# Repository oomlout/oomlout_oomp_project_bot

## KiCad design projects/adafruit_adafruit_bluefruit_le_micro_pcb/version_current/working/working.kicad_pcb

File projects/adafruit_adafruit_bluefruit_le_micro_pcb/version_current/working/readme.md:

# OOMP Project  
## Adafruit-Bluefruit-LE-Micro-PCB  by adafruit  
  
oomp key: oomp_projects_flat_adafruit_adafruit_bluefruit_le_micro_pcb  
(snippet of original readme)  
  
-- Adafruit Bluefruit LE Micro PCB (Discontinued)  
<a href="http://www.adafruit.com/products/2661"><br/>  
See the part listing in the Adafruit shop</a>  
  
DISCONTINUED  
Check out the [Adafruit Feather 32u4 Bluefruit LE](https://www.adafruit.com/products/2829), it's an awesome upgrade!  
  
PCB files for Adafruit Bluefruit LE Micro. Format is EagleCAD.  
- https://www.adafruit.com/product/2661  
  
--- License  
  
Adafruit invests time and resources providing this open source design, please support Adafruit and open-source hardware by purchasing products from [Adafruit](https://www.adafruit.com)!  
  
All text above must be included in any redistribution  
  
Designed by Limor Fried/Ladyada for Adafruit Industries.  
Creative Commons Attribution/Share-Alike, all text above must be included in any redistribution.   
See license.txt for additional information.  
  
  full source readme at [readme_src.md](readme_src.md)  
  
source repo at: [https://github.com/adafruit/Adafruit-Bluefruit-LE-Micro-PCB](https://github.com/adafruit/Adafruit-Bluefruit-LE-Micro-PCB)  
## Board  

## Schematic  

[schematic pdf](working_schematic.pdf)  
## Images

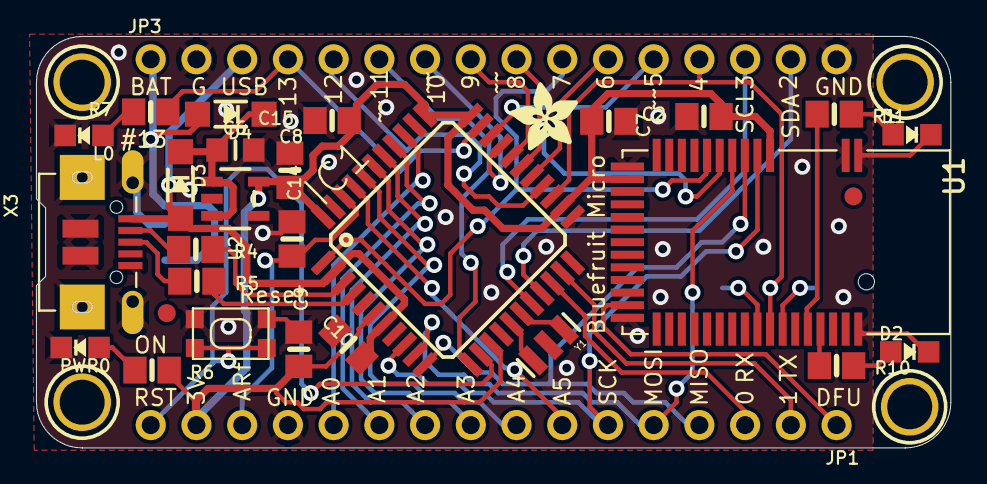
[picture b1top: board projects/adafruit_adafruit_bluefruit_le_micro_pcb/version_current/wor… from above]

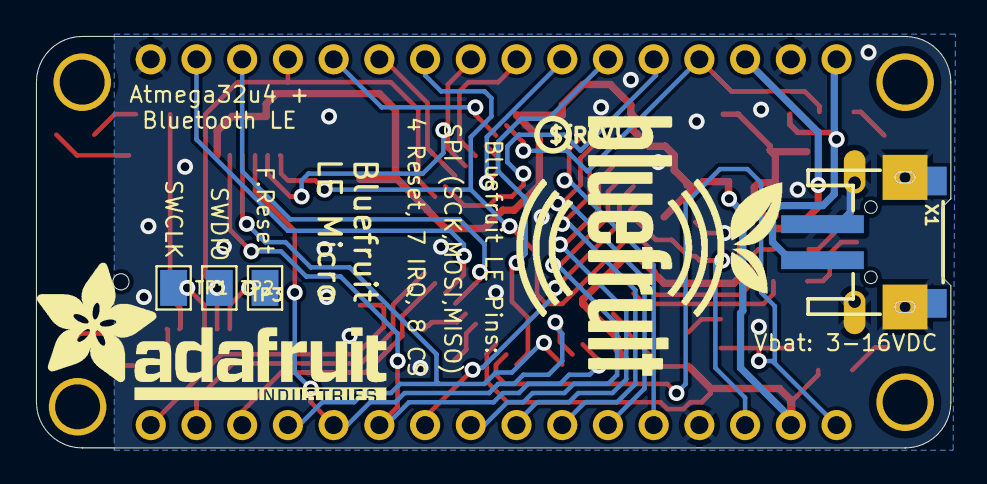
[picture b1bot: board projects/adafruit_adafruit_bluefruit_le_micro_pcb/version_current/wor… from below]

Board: 2 copper layers, 50.8 x 22.9 mm, 42 parts (7 on the bottom side), 45 nets.

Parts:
C2, C9: 1uF; 0805-NO
C6: 10µF; _0805MP
C7, C8: 10µF; 0805-NO
C10: 0.1uF; 0805_10MGAP
C14, C15: 0.1uF; 0805-NO
D1: RED; CHIPLED_0805_NOOUTLINE
D2: BLUE; CHIPLED_0805_NOOUTLINE
D3, D4: MBR120; SOD-123
IC1: ATMEGA32U4-AU; TQFP44
JP1, JP3: 1X16_ROUND
L0: RED; CHIPLED_0805_NOOUTLINE
PWR0: GREEN; CHIPLED_0805_NOOUTLINE
R1, R6, R7, R10: 2.2K; 0805-NO
R4, R5: 22; 0805-NO
SW1: SPST_TACT-KMR2; KMR2
TP1: SWCLK; PAD-1.5X2.0
TP2, TP3: SWDIO; PAD-1.5X2.0
U1: MBT40; BLE_MODULE_RAYTAC_MDBT40
U2: MIC5225-3.3; SOT23-5
U$6, U$24, U$31, U$32: MOUNTINGHOLE2.5; MOUNTINGHOLE_2.5_PLATED
U$7: ADAFRUIT_3.5MM
U$9: ADAFRUIT_TEXT_20MM
U$15: BLUEFRUITLOGO_150MM
U$23: PCBFEAT-REV-040
U$34, U$35: FIDUCIAL""; FIDUCIAL_1MM
X1: JSTPH; JSTPH2
X3: microUSB; 4UCONN_20329
Y1: 8MHz; RESONATOR-SMD

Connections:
0: IC1.20, JP1.3
1: IC1.21, JP1.2
2: IC1.19, JP3.15
3: IC1.18, JP3.14
4_SWDIO/RST: IC1.25, JP3.13, TP2.P$1, U1.35
5: IC1.31, JP3.12
6: IC1.27, JP3.11
7_BLE_IRQ: IC1.1, JP3.10, U1.8
8_BLE_CS: IC1.28, JP3.9, U1.7
9: IC1.29, JP3.8
10: IC1.30, JP3.7
11: IC1.12, JP3.6
12: IC1.26, JP3.5
13: IC1.32, JP3.4, R7.1
+3V3: C2.1, C7.1, C8.1, C9.1, C15.1, IC1.6, IC1.14, IC1.24, IC1.33, IC1.34, IC1.44, JP1.15, R6.2, U1.3, U1.14, U2.5
A0: IC1.36, JP1.12
A1: IC1.37, JP1.11
A2: IC1.38, JP1.10
A3: IC1.39, JP1.9
A4: IC1.40, JP1.8
A5: IC1.41, JP1.7
AREF: C14.1, IC1.42, JP1.14
CONNECTED: R10.1, U1.39
DFU: JP1.1, U1.24
FCTRYRST: TP3.P$1, U1.34
GND: C2.2, C6.2, C7.2, C8.2, C9.2, C10.2, C14.2, C15.2, D1.C, D2.C, IC1.5, IC1.15, IC1.23, IC1.35, IC1.43, JP1.13, JP3.2, JP3.16, L0.C, PWR0.C, SW1.2, SW1.4, U1.1, U1.2, U1.13, U1.16, U1.25, U1.42, U2.2, X1.1, X3.BASE@1, X3.BASE@2, X3.GND, X3.SPRT@1, X3.SPRT@2, X3.SPRT@3, X3.SPRT@4, Y1.2
MISO: IC1.11, JP1.4, U1.5
MODE: R1.1, U1.38
MOSI: IC1.10, JP1.5, U1.6
unnamed: L0.A, R7.2
unnamed: D1.A, R1.2
unnamed: D2.A, R10.2
unnamed: IC1.3, R4.2
unnamed: IC1.4, R5.2
unnamed: IC1.16, Y1.3
unnamed: IC1.17, Y1.1
unnamed: PWR0.A, R6.1
unnamed: R5.1, X3.D+
unnamed: R4.1, X3.D-
unnamed: C6.1, D3.C, D4.C, U2.1, U2.3
RST: IC1.13, JP1.16, SW1.1, SW1.3
SCK: IC1.9, JP1.6, U1.4
SWCLK: TP1.P$1, U1.36
VBAT: D4.A, JP3.1, X1.2
VBUS: C10.1, D3.A, IC1.2, IC1.7, JP3.3, X3.VBUS

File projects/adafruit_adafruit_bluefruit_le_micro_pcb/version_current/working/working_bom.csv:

Row,Description,Part,References,Value,Footprint,Quantity Per PCB,Status,Datasheet,BOM
1,,CAP_CERAMIC0805_10MGAP,C10,0.1uF,0805_10MGAP,1, ,,
2,,CAP_CERAMIC0805-NOOUTLINE,C14 C15,0.1uF,0805-NO,2, ,,
3,,CAP_CERAMIC0805-NOOUTLINE,C2 C9,1uF,0805-NO,2, ,,
4,,CAP_CERAMIC_0805MP,C6,10µF,_0805MP,1, ,,
5,,CAP_CERAMIC0805-NOOUTLINE,C7 C8,10µF,0805-NO,2, ,,
6,,LED0805_NOOUTLINE,D2,BLUE,CHIPLED_0805_NOOUTLINE,1, ,,
7,,DIODE-SCHOTTKYSOD-123,D3 D4,MBR120,SOD-123,2, ,,
8,,LED0805_NOOUTLINE,D1 L0,RED,CHIPLED_0805_NOOUTLINE,2, ,,
9,,ATMEGA32U4-AU,IC1,ATMEGA32U4-AU,TQFP44,1, ,,
10,,HEADER-1X16ROUND,JP1 JP3,HEADER-1X16ROUND,1X16_ROUND,2, ,,
11,,LED0805_NOOUTLINE,PWR0,GREEN,CHIPLED_0805_NOOUTLINE,1, ,,
12,,RESISTOR0805_NOOUTLINE,R4 R5,22,0805-NO,2, ,,
13,,RESISTOR0805_NOOUTLINE,R1 R6 R7 R10,2.2K,0805-NO,4, ,,
14,,SPST_TACT-KMR2,SW1,SPST_TACT-KMR2,KMR2,1, ,,
15,,NRF51822_MODULE_MDBT40,U1,MBT40,BLE_MODULE_RAYTAC_MDBT40,1, ,,
16,,VREG_SOT23-5,U2,MIC5225-3.3,SOT23-5,1, ,,
17,,CON_JST_PH_2PIN,X1,JSTPH,JSTPH2,1, ,,
18,,USBMICRO_20329,X3,microUSB,4UCONN_20329,1, ,,
19,,RESONATORSMD,Y1,RESONATORSMD,RESONATOR-SMD,1, ,,





Project info:
Schematic:,working
Variant:,default
Revision:,
Date:,2023-08-02_17-08-32
KiCad Version:,7.0.6-7.0.6~ubuntu22.04.1
Statistics:
Component Groups:,19
Component Count:,29 (0 SMD/ 0 THT)
Fitted Components:,29 (0 SMD/ 0 THT)
Number of PCBs:,1
Total Components:,29

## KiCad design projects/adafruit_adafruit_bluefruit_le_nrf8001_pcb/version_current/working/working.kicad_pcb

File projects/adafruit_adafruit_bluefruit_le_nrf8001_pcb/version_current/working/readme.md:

# Adafruit-Bluefruit-LE-nRF8001-PCB by adafruit  
This is a harvested standardized copy of a project from github.  
The original project can be found at:  
https://github.com/adafruit/Adafruit-Bluefruit-LE-nRF8001-PCB  
Please consult that link for additional, details, files, and license information.  
Note: It was auto harvested and if the original repo had more than one board file or anything out of the ordinary the files here are likely not representative.

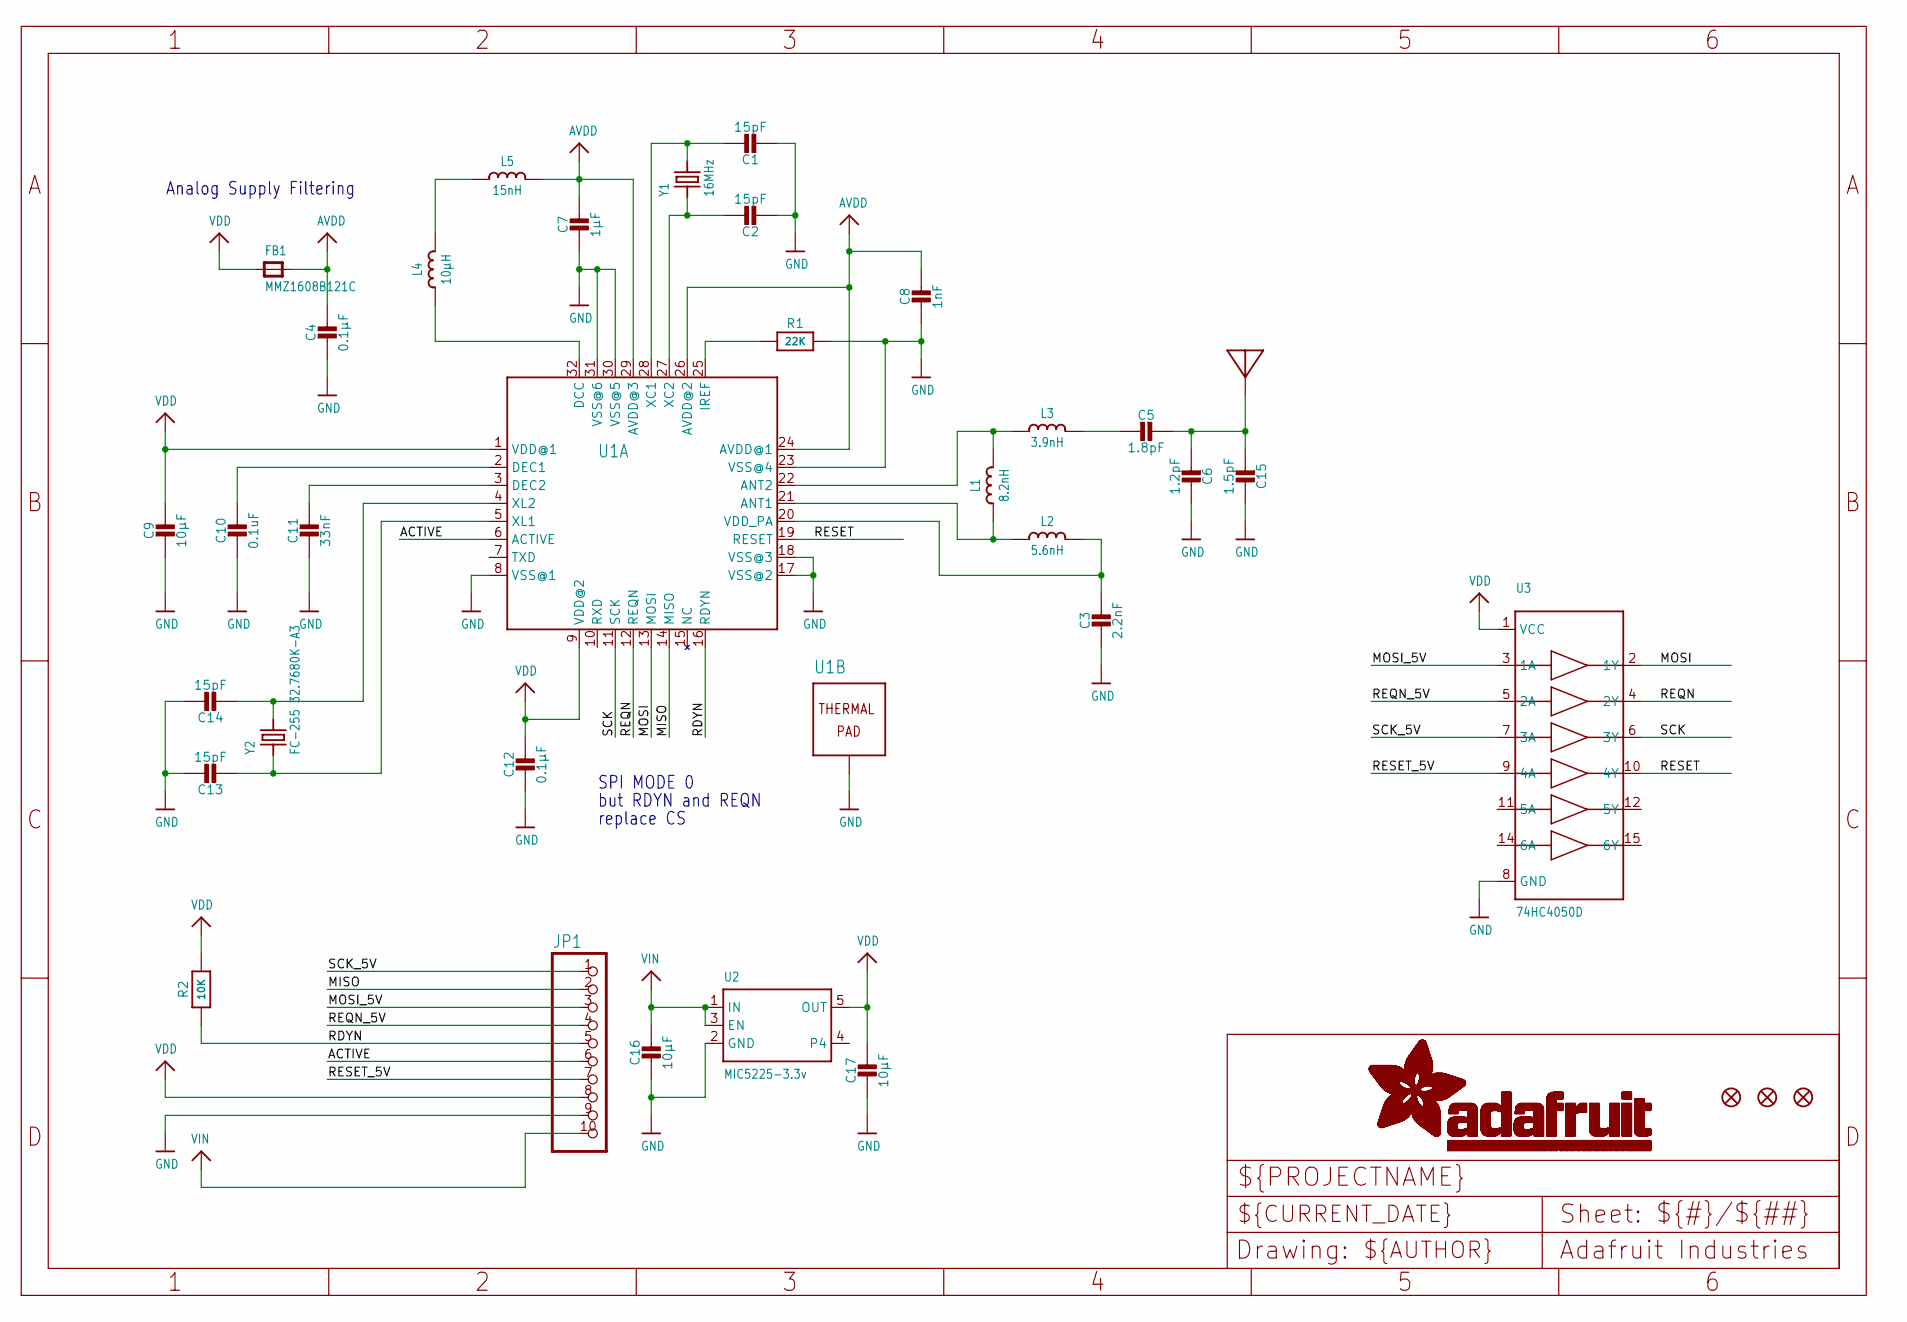
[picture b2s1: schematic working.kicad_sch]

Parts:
C1, C2, C13, C14: 15pF; 0805-NO
C3: 2.2nF; _0402
C4, C12: 0.1µF; 0805-NO
C5: 1.8pF; _0402MP
C6: 1.2pF; _0402MP
C7: 1µF; 0805-NO
C8: 1nF; _0603
C9, C16, C17: 10µF; 0805-NO
C10: 0.1uF; 0805-NO
C11: 33nF; 0805-NO
C15: 1.5pF; _0402MP
FB1: MMZ1608B121C; 0805
FID1, FID2, FID3: FIDUCIAL""; FIDUCIAL_1MM
JP1: HEADER-1X1070MIL; 1X10_ROUND70
L1: 8.2nH; _0402
L2: 5.6nH; _0402
L3: 3.9nH; _0402
L4: 10µH; _0603
L5: 15nH; _0603
R1: 22K; _0805MP
R2: 10K; 0805-NO
U1: nRF8001; QFN32_5MM
U2: MIC5225-3.3v; SOT23-5
U3: 74HC4050D; TSSOP16
U$28: ANTENNA_PCBNRF8001_1.6MM; ANT_PCB_2.4GHZ_NRF8001_1.6MM_1OZ
Y1: 16MHz; CRYSTAL_2.5X2
Y2: FC-255 32.7680K-A3; CRYSTAL_4.9X1.8

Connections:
ACTIVE: JP1.6, U1.6 (ACTIVE)
AVDD: C4.1, C7.1, C8.1, FB1.2, L5.2, U1.24 (AVDD@1), U1.26 (AVDD@2), U1.29 (AVDD@3)
GND: C1.2, C2.2, C3.2, C4.2, C6.1, C7.2, C8.2, C9.2, C10.2, C11.2, C12.2, C13.1, C14.1, C15.1, C16.2, C17.2, JP1.9, R1.2, U1.8 (VSS@1), U1.17 (VSS@2), U1.18 (VSS@3), U1.23 (VSS@4), U1.30 (VSS@5), U1.31 (VSS@6), U1.33 (TP), U2.2 (GND), U3.8 (GND)
MISO: JP1.2, U1.14 (MISO)
MOSI: U1.13 (MOSI), U3.2 (1Y)
MOSI_5V: JP1.3, U3.3 (1A)
unnamed: L1.2, L3.1, U1.22 (ANT2)
unnamed: L1.1, L2.1, U1.21 (ANT1)
unnamed: C3.1, L2.2, U1.20 (VDD_PA)
unnamed: L4.2, L5.1
unnamed: C5.2, L3.2
unnamed: C11.1, U1.3 (DEC2)
unnamed: C10.1, U1.2 (DEC1)
unnamed: C1.1, U1.28 (XC1), Y1.3 (2)
unnamed: C2.1, U1.27 (XC2), Y1.1
unnamed: L4.1, U1.32 (DCC)
unnamed: R1.1, U1.25 (IREF)
unnamed: C5.1, C6.2, C15.2, U$28.FEED
unnamed: C14.2, U1.4 (XL2), Y2.2
unnamed: C13.2, U1.5 (XL1), Y2.1
RDYN: JP1.5, R2.1, U1.16 (RDYN)
REQN: U1.12 (REQN), U3.4 (2Y)
REQN_5V: JP1.4, U3.5 (2A)
RESET: U1.19 (RESET), U3.10 (4Y)
RESET_5V: JP1.7, U3.9 (4A)
SCK: U1.11 (SCK), U3.6 (3Y)
SCK_5V: JP1.1, U3.7 (3A)
VDD: C9.1, C12.1, C17.1, FB1.1, JP1.8, R2.2, U1.1 (VDD@1), U1.9 (VDD@2), U2.5 (OUT), U3.1 (VCC)
VIN: C16.1, JP1.10, U2.1 (IN), U2.3 (EN)

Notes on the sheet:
but RDYN and REQN
SPI MODE 0
Analog Supply Filtering
replace CS

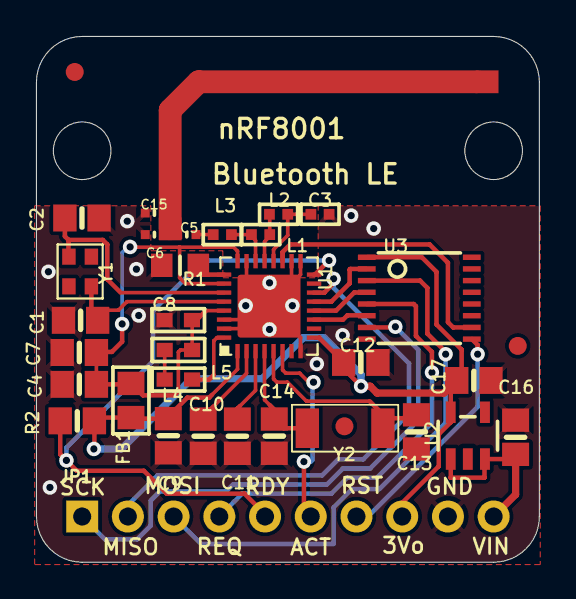
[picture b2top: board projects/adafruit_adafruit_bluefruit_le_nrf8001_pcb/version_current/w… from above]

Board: 2 copper layers, 27.9 x 29.2 mm, 38 parts (1 on the bottom side), 29 nets.

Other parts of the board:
@HOLE0, @HOLE1: (no value)
U$22: ADAFRUIT_TEXT_20MM

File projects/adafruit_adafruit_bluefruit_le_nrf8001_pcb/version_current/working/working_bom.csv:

Row,Description,Part,References,Value,Footprint,Quantity Per PCB,Status,Datasheet,BOM
1,,CAP_CERAMIC_0402MP,C6,1.2pF,_0402MP,1, ,,
2,,CAP_CERAMIC_0402MP,C15,1.5pF,_0402MP,1, ,,
3,,CAP_CERAMIC_0402MP,C5,1.8pF,_0402MP,1, ,,
4,,CAP_CERAMIC0805-NOOUTLINE,C1 C2 C13 C14,15pF,0805-NO,4, ,,
5,,CAP_CERAMIC_0603,C8,1nF,_0603,1, ,,
6,,CAP_CERAMIC_0402,C3,2.2nF,_0402,1, ,,
7,,CAP_CERAMIC0805-NOOUTLINE,C11,33nF,0805-NO,1, ,,
8,,CAP_CERAMIC0805-NOOUTLINE,C4 C10 C12,0.1µF,0805-NO,3, ,,
9,,CAP_CERAMIC0805-NOOUTLINE,C7,1µF,0805-NO,1, ,,
10,,CAP_CERAMIC0805-NOOUTLINE,C9 C16 C17,10µF,0805-NO,3, ,,
11,,FERRITE0805,FB1,MMZ1608B121C,0805,1, ,,
12,,HEADER-1X1070MIL,JP1,HEADER-1X1070MIL,1X10_ROUND70,1, ,,
13,,INDUCTOR_0402,L3,3.9nH,_0402,1, ,,
14,,INDUCTOR_0402,L2,5.6nH,_0402,1, ,,
15,,INDUCTOR_0402,L1,8.2nH,_0402,1, ,,
16,,INDUCTOR_0603,L5,15nH,_0603,1, ,,
17,,INDUCTOR_0603,L4,10µH,_0603,1, ,,
18,,RESISTOR0805_NOOUTLINE,R2,10K,0805-NO,1, ,,
19,,RESISTOR_0805MP,R1,22K,_0805MP,1, ,,
20,,74HC4050DTSSOP,U3,74HC4050D,TSSOP16,1, ,,
21,,VREG_SOT23-5,U2,MIC5225-3.3v,SOT23-5,1, ,,
22,,NRF8001,U1,nRF8001,QFN32_5MM,1, ,,
23,,ANTENNA_PCBNRF8001_1.6MM,U$28,ANTENNA_PCBNRF8001_1.6MM,ANT_PCB_2.4GHZ_NRF8001_1.6MM_1OZ,1, ,,
24,,CRYSTAL2.5X2.0,Y1,16MHz,CRYSTAL_2.5X2,1, ,,
25,,CRYSTAL4.9X1.8,Y2,FC-255 32.7680K-A3,CRYSTAL_4.9X1.8,1, ,,





Project info:
Schematic:,working
Variant:,default
Revision:,
Date:,2023-08-02_17-08-32
KiCad Version:,7.0.6-7.0.6~ubuntu22.04.1
Statistics:
Component Groups:,25
Component Count:,32 (0 SMD/ 0 THT)
Fitted Components:,32 (0 SMD/ 0 THT)
Number of PCBs:,1
Total Components:,32

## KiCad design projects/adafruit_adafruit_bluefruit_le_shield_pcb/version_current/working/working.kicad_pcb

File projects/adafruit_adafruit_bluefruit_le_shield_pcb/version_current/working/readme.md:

# Adafruit-Bluefruit-LE-Shield-PCB by adafruit  
This is a harvested standardized copy of a project from github.  
The original project can be found at:  
https://github.com/adafruit/Adafruit-Bluefruit-LE-Shield-PCB  
Please consult that link for additional, details, files, and license information.  
Note: It was auto harvested and if the original repo had more than one board file or anything out of the ordinary the files here are likely not representative.

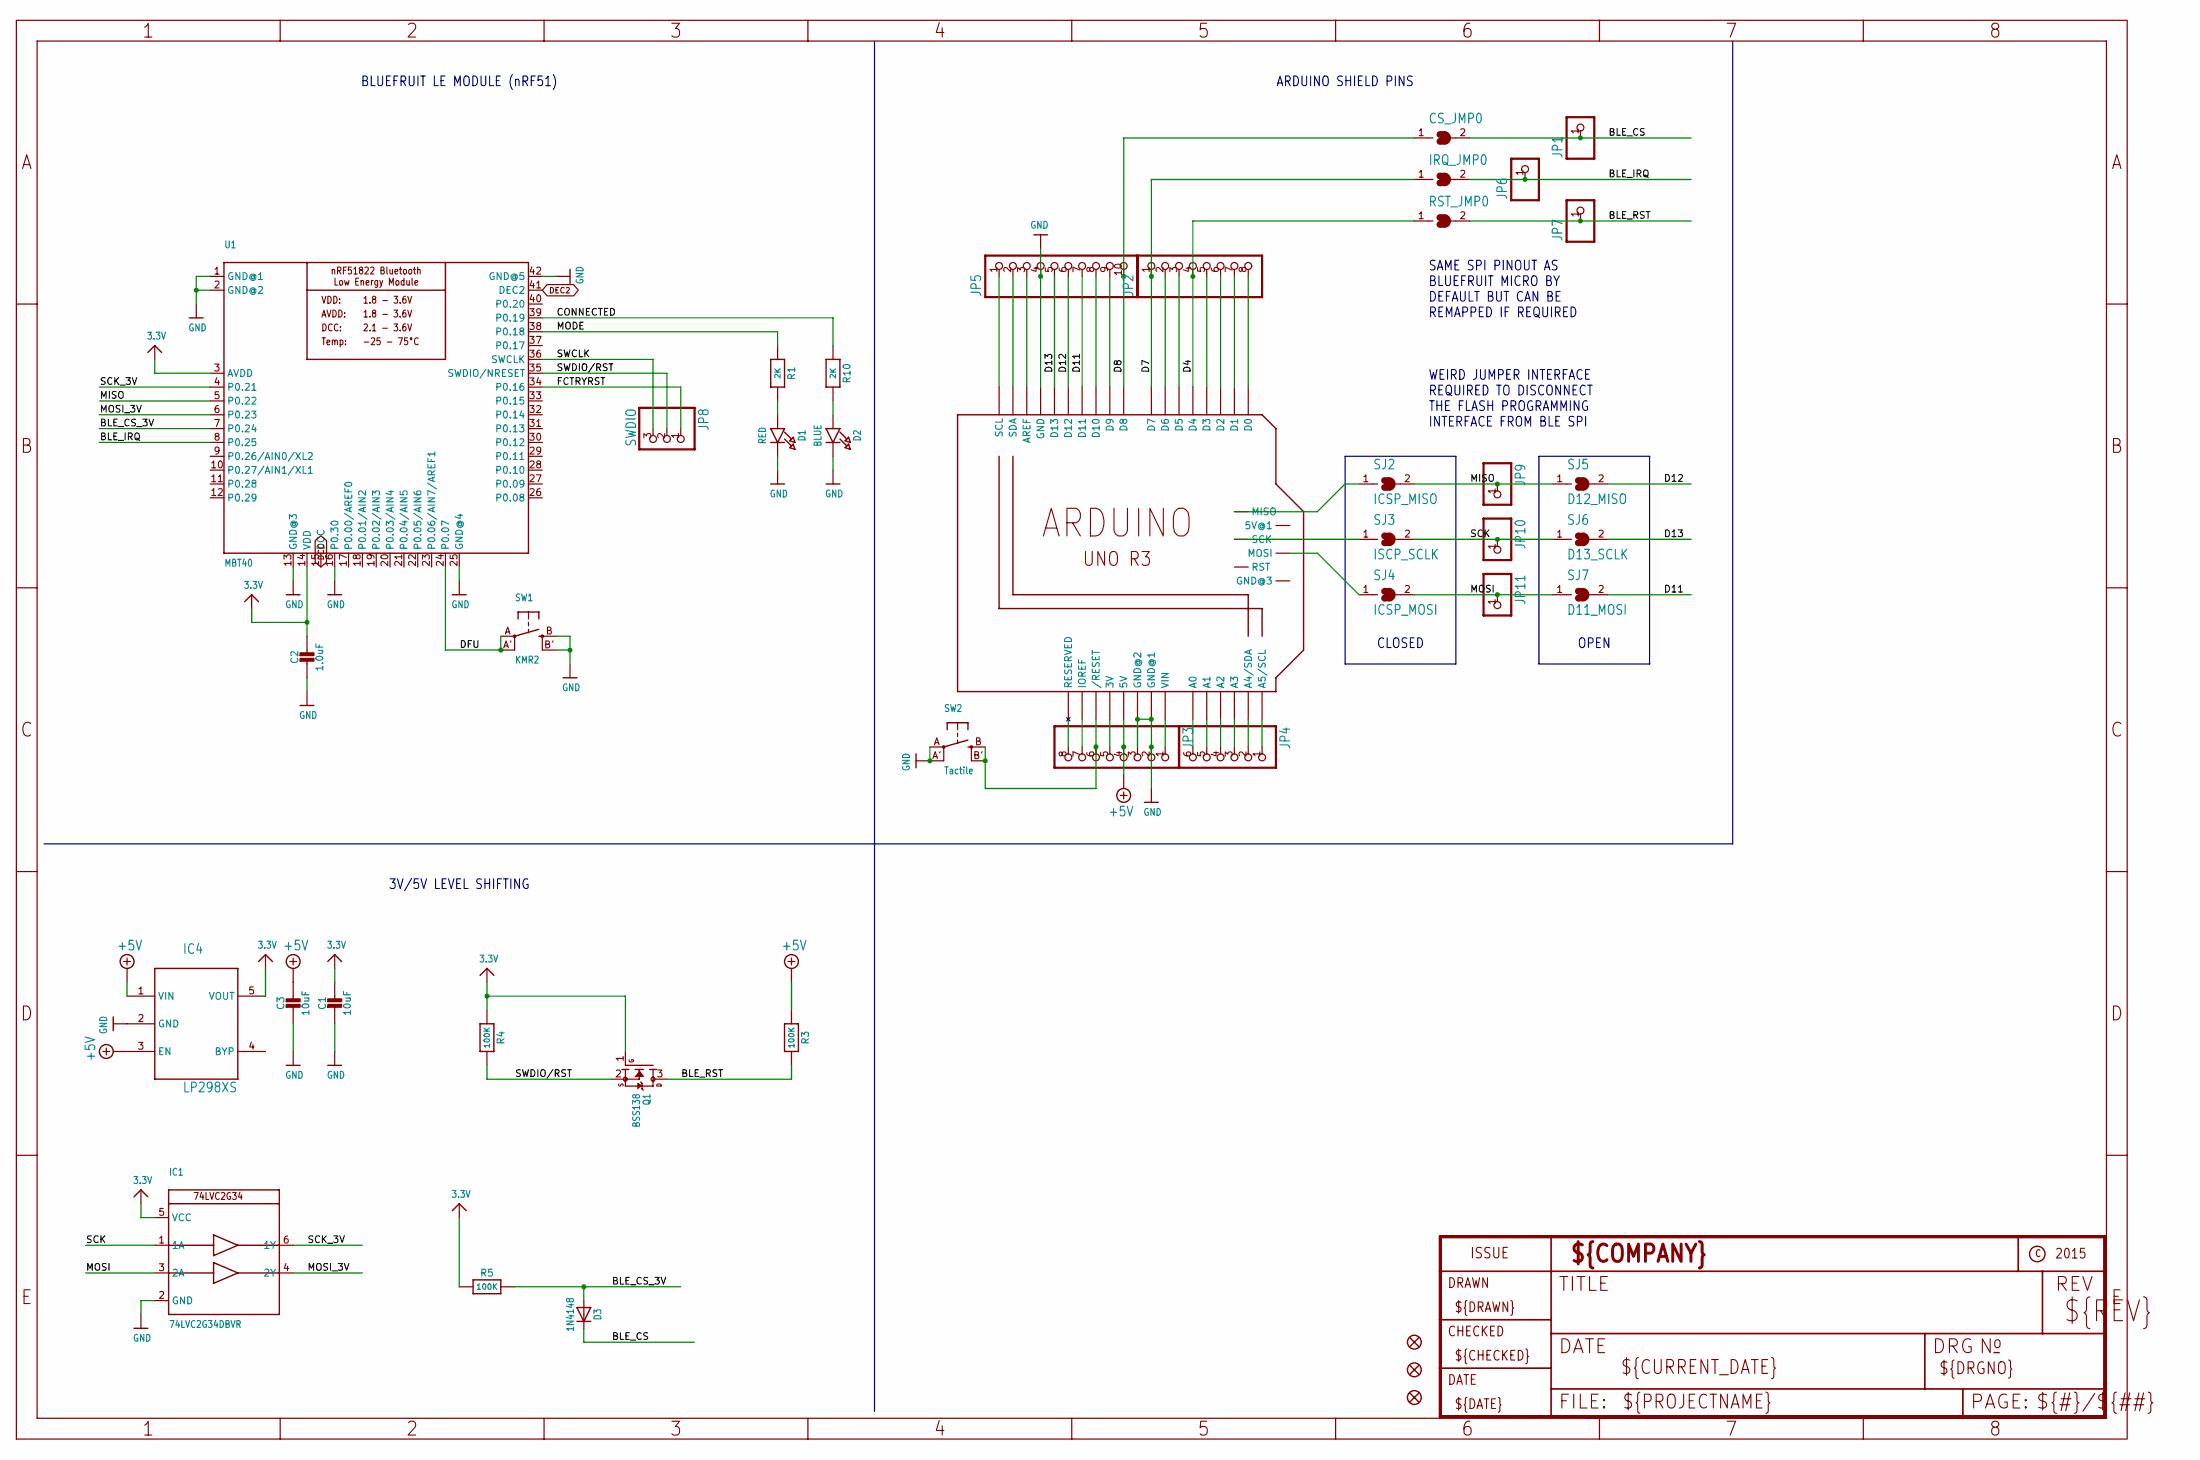
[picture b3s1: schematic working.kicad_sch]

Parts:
C1, C3: 10uF; 0805-NO
C2: 1.0uF; 0805-NO
CS_JMP0: SOLDERJUMPERCLOSED; SOLDERJUMPER_CLOSEDWIRE
D1: RED; CHIPLED_0805_NOOUTLINE
D2: BLUE; CHIPLED_0805_NOOUTLINE
D3: 1N4148; SOD-323
FID1, FID2, FID3: FIDUCIAL""; FIDUCIAL_1MM
IC1: 74LVC2G34DBVR; SOT23-6
IC4: LP298XS; SOT23-5L
IRQ_JMP0: SOLDERJUMPERCLOSED; SOLDERJUMPER_CLOSEDWIRE
JP1, JP6, JP7, JP9, JP10, JP11: HEADER-1X1ROUND; 1X01_ROUND
JP2, JP3: HEADER-1X870MIL; 1X08_ROUND_70
JP4: HEADER-1X670MIL; 1X06_ROUND_70
JP5: HEADER-1X1070MIL; 1X10_ROUND70
JP8: SWDIO; 1X03_ROUND_76
M1: ARDUINO_R3_ICSP_NODIM; ARDUINOR3_ICSP_NODIM
Q1: BSS138; SOT23-WIDE
R1, R10: 2K; 0805-NO
R3, R4, R5: 100K; 0805-NO
RST_JMP0: SOLDERJUMPERCLOSED; SOLDERJUMPER_CLOSEDWIRE
SJ2: ICSP_MISO; SOLDERJUMPER_CLOSEDWIRE
SJ3: ISCP_SCLK; SOLDERJUMPER_CLOSEDWIRE
SJ4: ICSP_MOSI; SOLDERJUMPER_CLOSEDWIRE
SJ5: D12_MISO; SOLDERJUMPER_REFLOW_NOPASTE
SJ6: D13_SCLK; SOLDERJUMPER_REFLOW_NOPASTE
SJ7: D11_MOSI; SOLDERJUMPER_REFLOW_NOPASTE
SW1: KMR2; BTN_KMR2_4.6X2.8
SW2: Tactile; EVQ-Q2
U1: MBT40; BLE_MODULE_RAYTAC_MDBT40

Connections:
3.3V: C1.1, C2.1, IC1.5 (VCC), IC4.5 (VOUT), Q1.1 (G), R4.1, R5.1, U1.3 (AVDD), U1.14 (VDD)
+3V: JP3.5, M1.3V
+5V: C3.1, IC4.1 (VIN), IC4.3 (EN), JP3.4, M1.5V, R3.1
A0: JP4.6, M1.A0
A1: JP4.5, M1.A1
A2: JP4.4, M1.A2
A3: JP4.3, M1.A3
A4: JP4.2, M1.A4 (A4/SDA)
A5: JP4.1, M1.A5 (A5/SCL)
AREF: JP5.3, M1.AREF
BLE_CS: CS_JMP0.2, D3.C, JP1.1
BLE_CS_3V: D3.A, R5.2, U1.7 (P0.24)
BLE_IRQ: IRQ_JMP0.2, JP6.1, U1.8 (P0.25)
BLE_RST: JP7.1, Q1.3 (D), R3.2, RST_JMP0.2
CONNECTED: R10.1, U1.39 (P0.19)
D4: JP2.4, M1.D4, RST_JMP0.1
D7: IRQ_JMP0.1, JP2.1, M1.D7
D8: CS_JMP0.1, JP5.10, M1.D8
D11: JP5.7, M1.D11, SJ7.2
D12: JP5.6, M1.D12, SJ5.2
D13: JP5.5, M1.D13, SJ6.2
DCC: U1.15 (DCC)
DEC2: U1.41 (DEC2)
DFU: SW1.A, SW1.A' (P1), U1.24 (P0.07)
FCTRYRST: JP8.1, U1.34 (P0.16)
GND: C1.2, C2.2, C3.2, D1.C, D2.C, IC1.2 (GND), IC4.2 (GND), JP3.2, JP3.3, JP5.4, M1.GND, M1.GND@1 (GND@2), M1.GND@3 (GND@1), SW1.B (S), SW1.B' (S1), SW2.A, SW2.A' (P1), U1.1 (GND@1), U1.2 (GND@2), U1.13 (GND@3), U1.16 (P0.30), U1.25 (GND@4), U1.42 (GND@5)
IOREF: JP3.7, M1.IOREF
MISO: JP9.1, SJ2.2, SJ5.1, U1.5 (P0.22)
MISO_ICSP: M1.MISO, SJ2.1
MODE: R1.1, U1.38 (P0.18)
MOSI: IC1.3 (2A), JP11.1, SJ4.2, SJ7.1
MOSI_3V: IC1.4 (2Y), U1.6 (P0.23)
MOSI_ICSP: M1.MOSI, SJ4.1
unnamed: D1.A, R1.2
unnamed: D2.A, R10.2
unnamed: JP2.2, M1.D6
unnamed: JP2.3, M1.D5
unnamed: JP2.5, M1.D3
unnamed: JP2.6, M1.D2
unnamed: JP2.7, M1.D1
unnamed: JP2.8, M1.D0
unnamed: JP5.8, M1.D10
unnamed: JP5.9, M1.D9
NC: JP3.8, M1.RESERVED
RESET: JP3.6, M1.RESET (/RESET), SW2.B (S), SW2.B' (S1)
SCK: IC1.1 (1A), JP10.1, SJ3.2, SJ6.1
SCK_3V: IC1.6 (1Y), U1.4 (P0.21)
SCK_ICSP: M1.SCK, SJ3.1
SCL: JP5.1, M1.SCL
SDA: JP5.2, M1.SDA
SWCLK: JP8.3, U1.36 (SWCLK)
SWDIO/RST: JP8.2, Q1.2 (S), R4.2, U1.35 (SWDIO/NRESET)
VIN: JP3.1, M1.VIN

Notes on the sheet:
BLUEFRUIT LE MODULE (nRF51)
SAME SPI PINOUT AS BLUEFRUIT MICRO BY DEFAULT BUT CAN BE REMAPPED IF REQUIRED
ARDUINO SHIELD PINS
WEIRD JUMPER INTERFACE REQUIRED TO DISCONNECT THE FLASH PROGRAMMING INTERFACE FROM BLE SPI
OPEN
CLOSED
3V/5V LEVEL SHIFTING

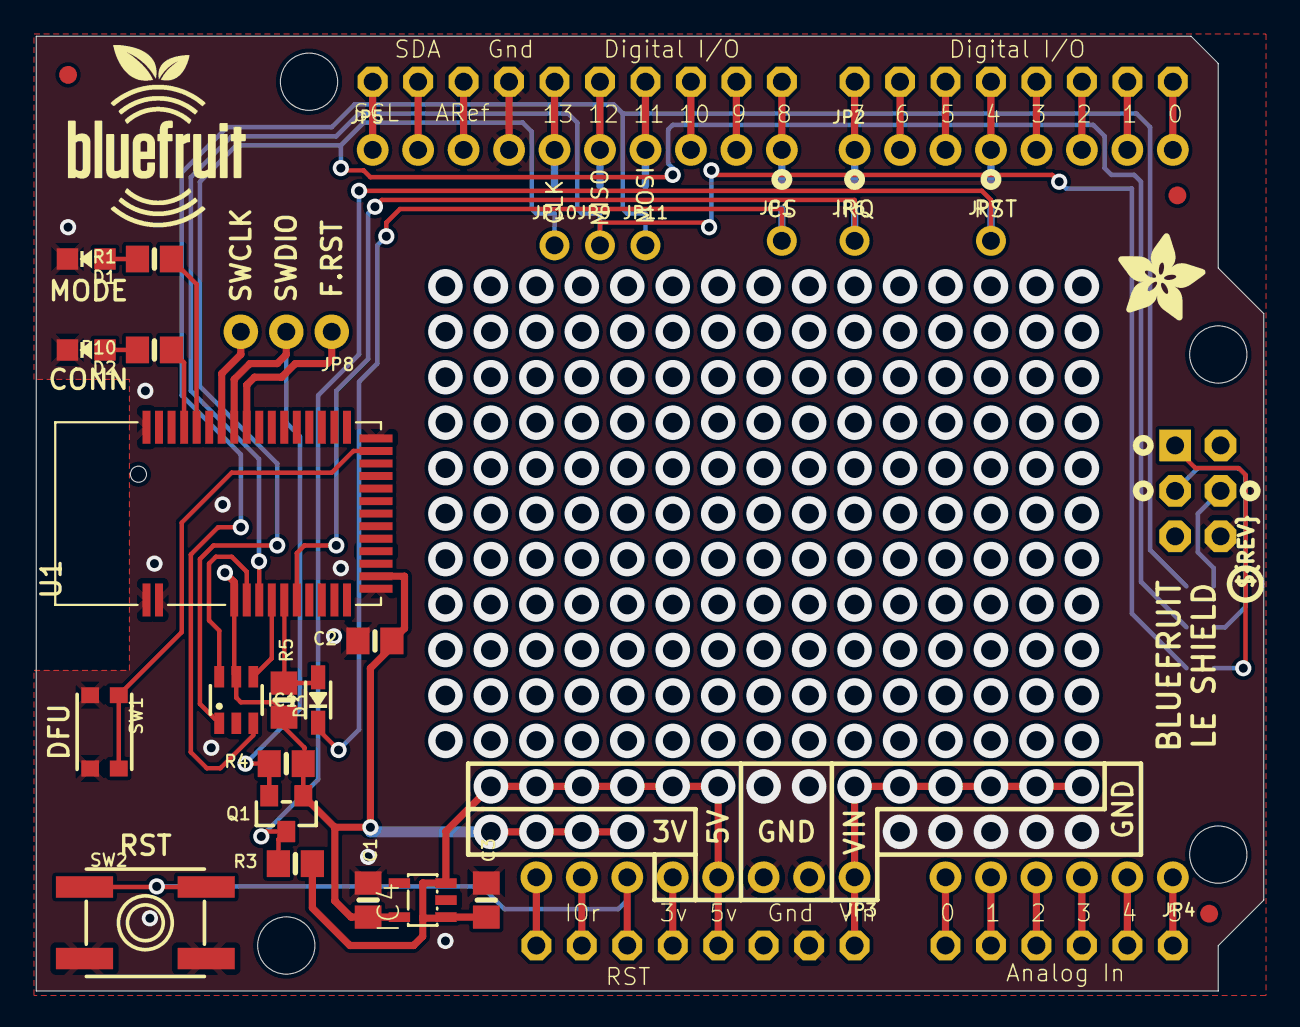
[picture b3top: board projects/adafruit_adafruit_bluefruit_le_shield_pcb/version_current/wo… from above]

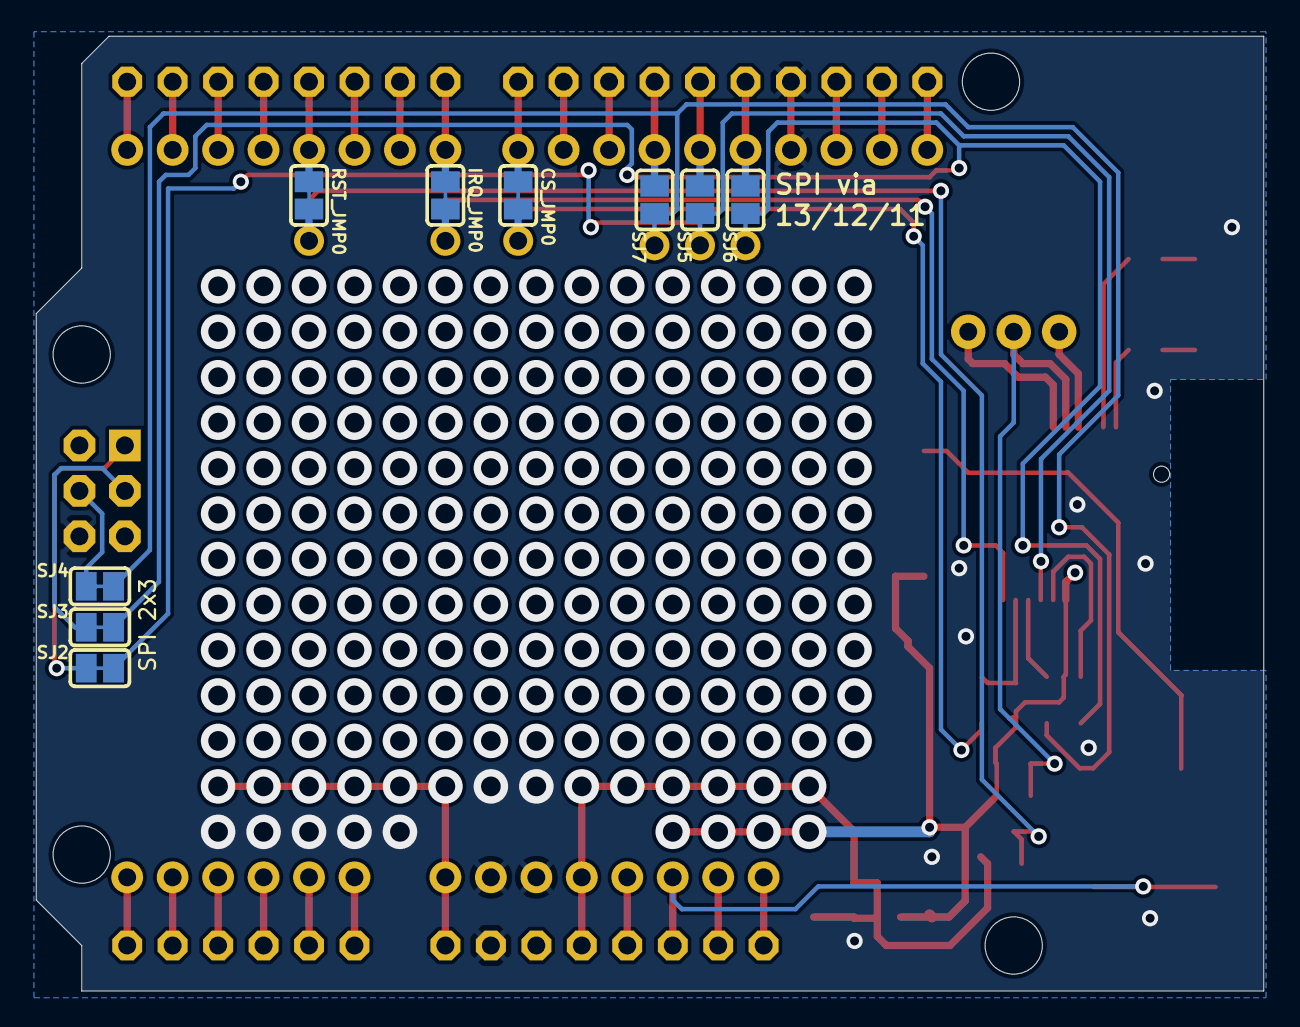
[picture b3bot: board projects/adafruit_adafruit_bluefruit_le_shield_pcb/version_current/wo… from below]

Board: 2 copper layers, 68.6 x 53.3 mm, 48 parts (9 on the bottom side), 51 nets.

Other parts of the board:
@HOLE0, @HOLE1, @HOLE2, @HOLE3: (no value)
U$8: BLUEFRUITLOGO_100MM
U$9: ADAFRUIT_5MM
U$21: PCBFEAT-REV-040

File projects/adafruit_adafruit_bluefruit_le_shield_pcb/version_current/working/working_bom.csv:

Row,Description,Part,References,Value,Footprint,Quantity Per PCB,Status,Datasheet
1,,CAP_CERAMIC0805-NOOUTLINE,C2,1.0uF,0805-NO,1, ,
2,,CAP_CERAMIC0805-NOOUTLINE,C1 C3,10uF,0805-NO,2, ,
3,,DIODESOD-323,D3,1N4148,SOD-323,1, ,
4,,LED0805_NOOUTLINE,D2,BLUE,CHIPLED_0805_NOOUTLINE,1, ,
5,,LED0805_NOOUTLINE,D1,RED,CHIPLED_0805_NOOUTLINE,1, ,
6,,74LVC2G34DBVR,IC1,74LVC2G34DBVR,SOT23-6,1, ,
7,,LP298XS,IC4,LP298XS,SOT23-5L,1, ,
8,,HEADER-1X1070MIL,JP5,HEADER-1X1070MIL,1X10_ROUND70,1, ,
9,,HEADER-1X1ROUND,JP1 JP6 JP7 JP9 JP10 JP11,HEADER-1X1ROUND,1X01_ROUND,6, ,
10,,HEADER-1X670MIL,JP4,HEADER-1X670MIL,1X06_ROUND_70,1, ,
11,,HEADER-1X870MIL,JP2 JP3,HEADER-1X870MIL,1X08_ROUND_70,2, ,
12,,HEADER-1X376MIL,JP8,SWDIO,1X03_ROUND_76,1, ,
13,,ARDUINO_R3_ICSP_NODIM,M1,ARDUINO_R3_ICSP_NODIM,ARDUINOR3_ICSP_NODIM,1, ,
14,,MOSFET-NWIDE,Q1,BSS138,SOT23-WIDE,1, ,
15,,RESISTOR0805_NOOUTLINE,R1 R10,2K,0805-NO,2, ,
16,,RESISTOR0805_NOOUTLINE,R3 R4 R5,100K,0805-NO,3, ,
17,,SWITCH_TACT_SMT4.6X2.8,SW1,KMR2,BTN_KMR2_4.6X2.8,1, ,
18,,SWITCH_TACT_SMT,SW2,Tactile,EVQ-Q2,1, ,
19,,NRF51822_MODULE_MDBT40,U1,MBT40,BLE_MODULE_RAYTAC_MDBT40,1, ,





Project info:
Schematic:,working
Variant:,default
Revision:,
Date:,2023-08-02_17-08-32
KiCad Version:,7.0.6-7.0.6~ubuntu22.04.1
Statistics:
Component Groups:,19
Component Count:,29 (0 SMD/ 0 THT)
Fitted Components:,29 (0 SMD/ 0 THT)
Number of PCBs:,1
Total Components:,29

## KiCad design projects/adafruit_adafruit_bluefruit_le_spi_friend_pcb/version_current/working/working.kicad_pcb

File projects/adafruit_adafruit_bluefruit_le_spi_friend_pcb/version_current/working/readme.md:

# Adafruit-Bluefruit-LE-SPI-Friend-PCB by adafruit  
This is a harvested standardized copy of a project from github.  
The original project can be found at:  
https://github.com/adafruit/Adafruit-Bluefruit-LE-SPI-Friend-PCB  
Please consult that link for additional, details, files, and license information.  
Note: It was auto harvested and if the original repo had more than one board file or anything out of the ordinary the files here are likely not representative.

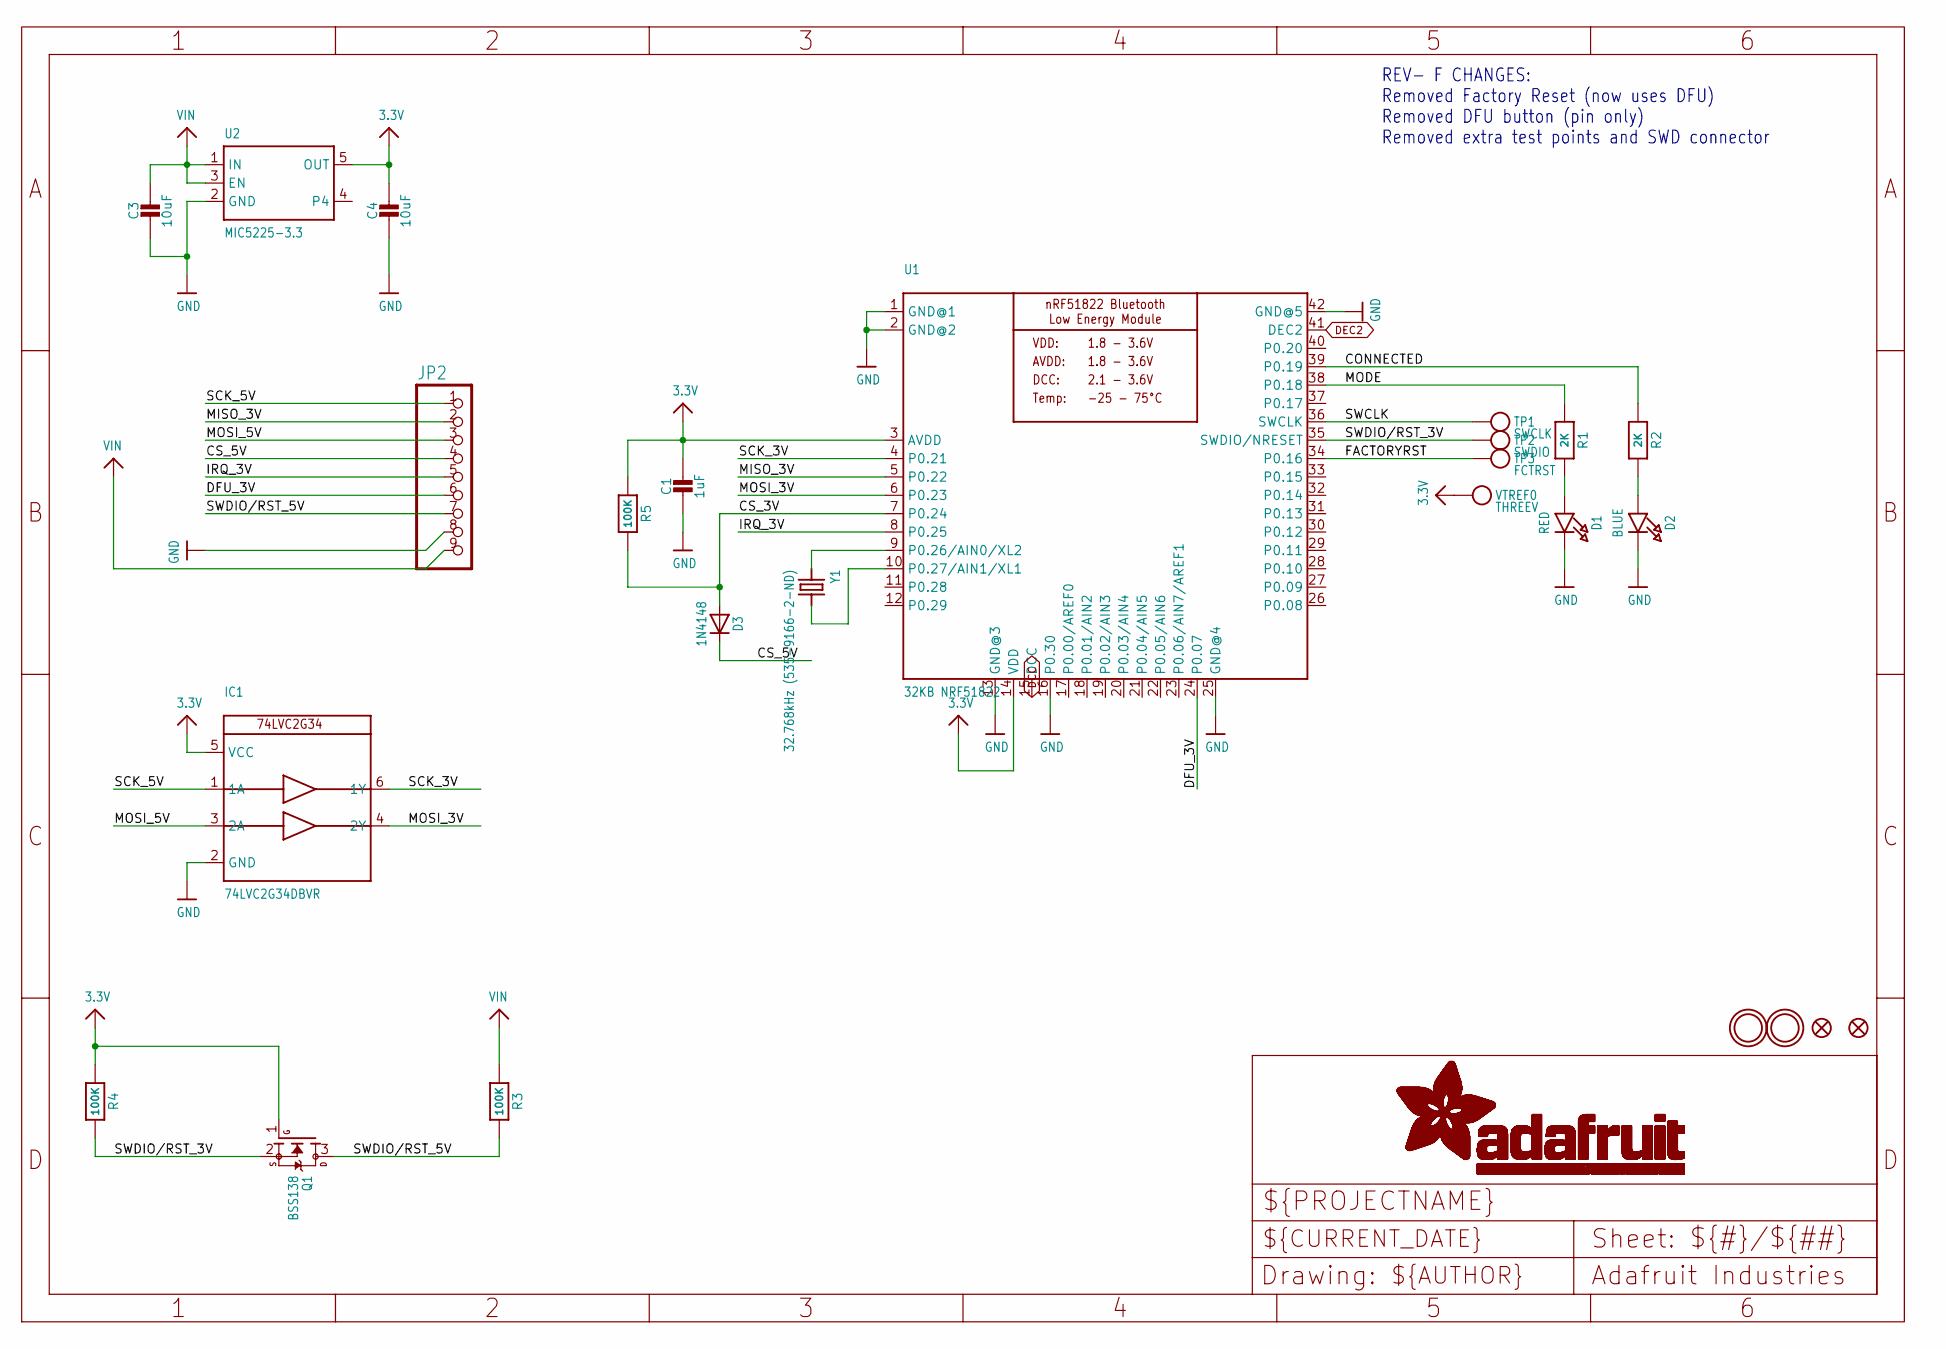
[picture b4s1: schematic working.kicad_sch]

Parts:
C1: 1uF; 0805_10MGAP
C3: 10uF; 0805-NO
C4: 10uF; 0805_10MGAP
D1: RED; CHIPLED_0805_NOOUTLINE
D2: BLUE; CHIPLED_0805_NOOUTLINE
D3: 1N4148; SOD-323
FID1, FID3: FIDUCIAL""; FIDUCIAL_1MM
IC1: 74LVC2G34DBVR; SOT23-6
JP2: HEADER-1X970MIL; 1X09_ROUND_70
Q1: BSS138; SOT23-WIDE@1
R1, R2: 2K; _0805MP
R3, R4: 100K; 0805-NO
R5: 100K; _0805MP
TP1: SWCLK; PAD-1.5X2.0
TP2: SWDIO; PAD-1.5X2.0
TP3: FCTRST; PAD-1.5X2.0
U1: 32KB NRF51822; BLE_MODULE_RAYTAC_MDBT40
U2: MIC5225-3.3; SOT23-5
U$28, U$29: MOUNTINGHOLE2.5; MOUNTINGHOLE_2.5_PLATED
VTREF0: THREEV; PAD-1.5X2.0
Y1: 32.768kHz (535-9166-2-ND); CRYSTAL_CYL_2X6MM_SMT

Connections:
3.3V: C1.1, C4.1, IC1.5 (VCC), Q1.1 (G), R4.1, R5.1, U1.3 (AVDD), U1.14 (VDD), U2.5 (OUT), VTREF0.P$1
CONNECTED: R2.1, U1.39 (P0.19)
CS_3V: D3.A, R5.2, U1.7 (P0.24)
CS_5V: D3.C, JP2.4
DCC: U1.15 (DCC)
DEC2: U1.41 (DEC2)
DFU_3V: JP2.6, U1.24 (P0.07)
FACTORYRST: TP3.P$1, U1.34 (P0.16)
GND: C1.2, C3.2, C4.2, D1.C, D2.C, IC1.2 (GND), JP2.8, U1.1 (GND@1), U1.2 (GND@2), U1.13 (GND@3), U1.16 (P0.30), U1.25 (GND@4), U1.42 (GND@5), U2.2 (GND)
IRQ_3V: JP2.5, U1.8 (P0.25)
MISO_3V: JP2.2, U1.5 (P0.22)
MODE: R1.1, U1.38 (P0.18)
MOSI_3V: IC1.4 (2Y), U1.6 (P0.23)
MOSI_5V: IC1.3 (2A), JP2.3
unnamed: U1.9 (P0.26/AIN0/XL2), Y1.1
unnamed: U1.10 (P0.27/AIN1/XL1), Y1.2
unnamed: D1.A, R1.2
unnamed: D2.A, R2.2
SCK_3V: IC1.6 (1Y), U1.4 (P0.21)
SCK_5V: IC1.1 (1A), JP2.1
SWCLK: TP1.P$1, U1.36 (SWCLK)
SWDIO/RST_3V: Q1.2 (S), R4.2, TP2.P$1, U1.35 (SWDIO/NRESET)
SWDIO/RST_5V: JP2.7, Q1.3 (D), R3.2
VIN: C3.1, JP2.9, R3.1, U2.1 (IN), U2.3 (EN)

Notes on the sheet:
REV- F CHANGES: Removed Factory Reset (now uses DFU) Removed DFU button (pin only) Removed extra test points and SWD connector
